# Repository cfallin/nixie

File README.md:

These are the raw Eagle schematic/PCB design files and the AVR firmware for a
Nixie tube clock.

Nixie tubes are gas-discharge neon display tubes. They take ~150 volts at a few
milliamps and glow a soft, pleasing orange. Each digit is a separate cathode in
a particular shape, so the numerals look more natural than more contemprary
7-segment display designs.

This project is a small microcontroller-based digital clock using 6 nixie tubes
(for HH:MM:SS). An ATmega16 8-bit AVR microcontroller keeps time based on its
20MHz system clock provided by a crystal oscillator, and controls six digit
driver ICs, one per Nixie tube. Each driver has high-voltage open-collector
outputs capable of directly interfacing with the display tube cathodes. The 150
volt anode supply is provided by a small switched-inductor boost converter,
which uses a power MOSFET driven by the microcontroller's PWM generator. The
design includes a feedback loop to an analog-to-digital (ADC) input on the AVR
so that it can regulate the tube voltage precisely.

Nixies can be found in various places online and often come from Russia. I
found mine on Etsy. Prices vary but I think the retro glow is well worth the
cost :-) The 74141 Nixie driver chips are also somewhat rare (e.g., not stocked
by Digikey) but can be found on eBay or at other small shops online.

=== DEVELOPMENT ENVIRONMENT ===

The firmware is written in C to be cross-compiled by avr-gcc. It assumes the
standard AVR headers that come with that compiler. The Makefile includes a
target to program the flash and fuses on the AVR using avrdude, but other
programmers can also be used.

The schematic and board were drawn in Eagle CAD. The additional libraries used
are included here.

=== IN PROGRESS ===

Work is currently in progress; in particular, the firmware is specific to an
earlier (hand-built) prototype version of the hardware and DOES NOT MATCH the
board. The board is currently (Feb 2014) out for a prototype run; when I build
the hardware designed here I'll update the firmware as appropriate.

=== LICENSE ===

All code, schematics and board design files here are Copyright (c) 2014 Chris
Fallin <cfallin@c1f.net>. Provided under the GNU GPL v2.

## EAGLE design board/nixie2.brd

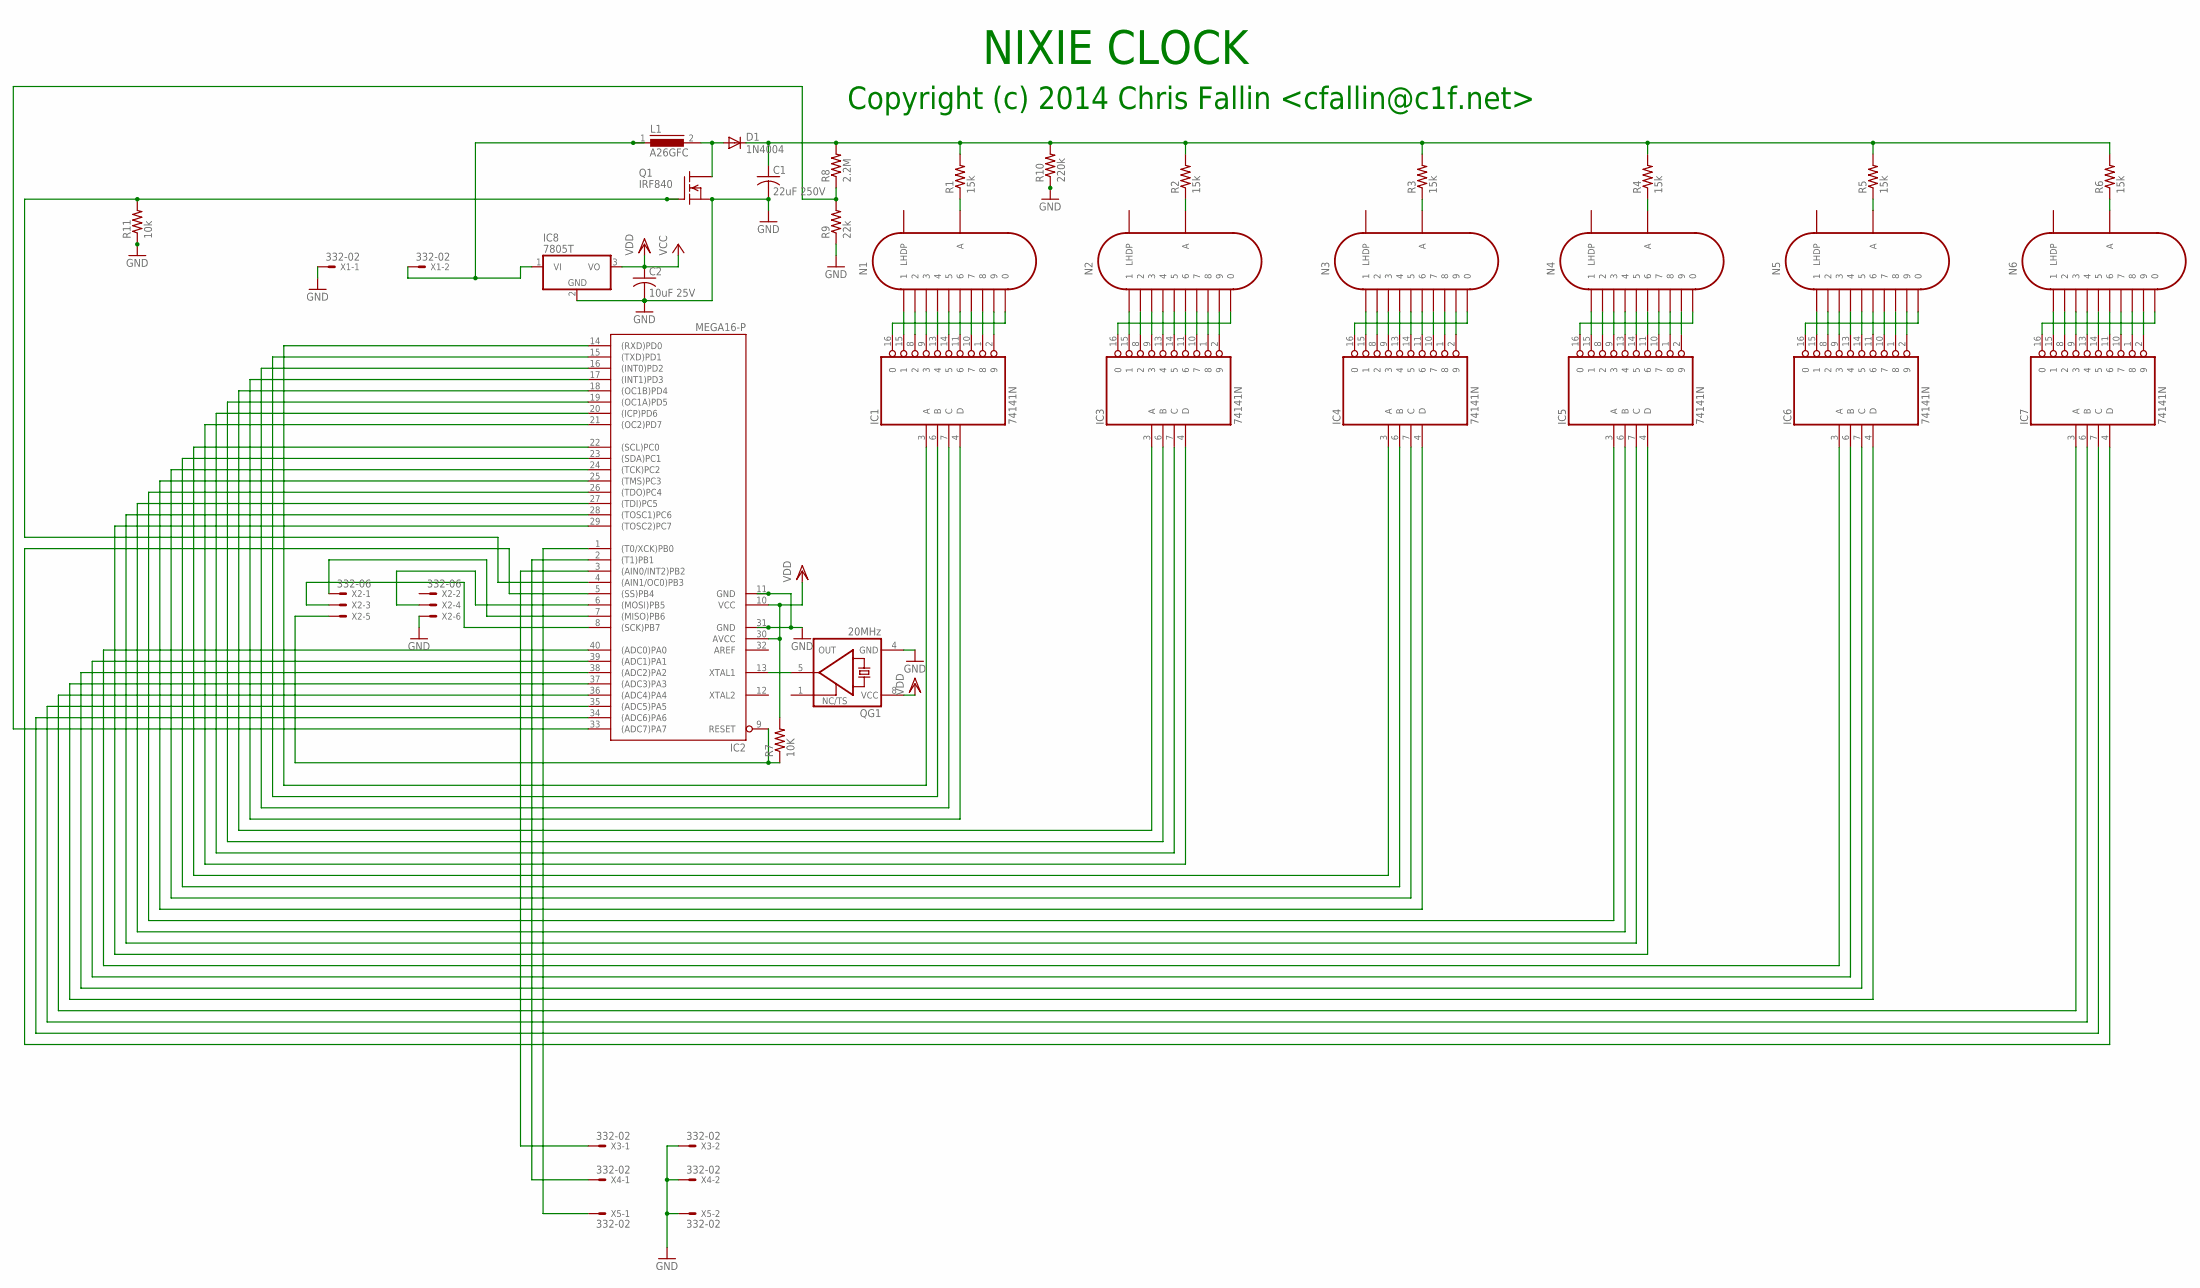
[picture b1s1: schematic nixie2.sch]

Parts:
C1: 22uF 250V; C050-075X075
C2: 10uF 25V; C050-075X075
D1: 1N4004; DO41-10
IC1, IC3, IC4, IC5, IC6, IC7: 74141N; DIL16
IC2: MEGA16-P; DIL40
IC8: 7805T; TO220H
L1: A26GFC
N1, N2, N3, N4, N5, N6: IN-12B; IN-12
Q1: IRF840; TO220
QG1: 20MHz; DIL08S
R1, R2, R3, R4, R5, R6: 15k; 0204V
R7: 10K; 0204V
R8: 2.2M; 0204V
R9: 22k; 0204V
R10: 220k; 0204V
R11: 10k; 0204V
X1, X3, X4, X5: 332-02
X2: 332-06

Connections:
GND: C1.2, C2.2, IC1.12 (GND), IC2.11 (GND), IC2.31 (GND), IC3.12 (GND), IC4.12 (GND), IC5.12 (GND), IC6.12 (GND), IC7.12 (GND), IC8.2 (GND), Q1.3 (S), QG1.4 (GND), R9.1, R10.1, R11.1, X1.1, X2.6, X3.2, X4.2, X5.2
unnamed: IC1.15 (1), N1.1
unnamed: IC1.8 (2), N1.2
unnamed: IC1.9 (3), N1.3
unnamed: IC1.13 (4), N1.4
unnamed: IC1.14 (5), N1.5
unnamed: IC1.11 (6), N1.6
unnamed: IC1.10 (7), N1.7
unnamed: IC1.1 (8), N1.8
unnamed: IC1.2 (9), N1.9
unnamed: N1.A, R1.1
unnamed: IC3.15 (1), N2.1
unnamed: IC3.8 (2), N2.2
unnamed: IC3.9 (3), N2.3
unnamed: IC3.13 (4), N2.4
unnamed: IC3.14 (5), N2.5
unnamed: IC3.11 (6), N2.6
unnamed: IC3.10 (7), N2.7
unnamed: IC3.1 (8), N2.8
unnamed: IC3.2 (9), N2.9
unnamed: IC3.16 (0), N2.0
unnamed: N2.A, R2.1
unnamed: IC4.15 (1), N3.1
unnamed: IC4.8 (2), N3.2
unnamed: IC4.9 (3), N3.3
unnamed: IC4.13 (4), N3.4
unnamed: IC4.14 (5), N3.5
unnamed: IC4.11 (6), N3.6
unnamed: IC4.10 (7), N3.7
unnamed: IC4.1 (8), N3.8
unnamed: IC4.2 (9), N3.9
unnamed: IC4.16 (0), N3.0
unnamed: N3.A, R3.1
unnamed: IC5.15 (1), N4.1
unnamed: IC5.8 (2), N4.2
unnamed: IC5.9 (3), N4.3
unnamed: IC5.13 (4), N4.4
unnamed: IC5.14 (5), N4.5
unnamed: IC5.11 (6), N4.6
unnamed: IC5.10 (7), N4.7
unnamed: IC5.1 (8), N4.8
unnamed: IC5.2 (9), N4.9
unnamed: IC5.16 (0), N4.0
unnamed: N4.A, R4.1
unnamed: IC6.15 (1), N5.1
unnamed: IC6.8 (2), N5.2
unnamed: IC6.9 (3), N5.3
unnamed: IC6.13 (4), N5.4
unnamed: IC6.14 (5), N5.5
unnamed: IC6.11 (6), N5.6
unnamed: IC6.10 (7), N5.7
unnamed: IC6.1 (8), N5.8
unnamed: IC6.2 (9), N5.9
unnamed: IC6.16 (0), N5.0
unnamed: N5.A, R5.1
unnamed: IC7.15 (1), N6.1
unnamed: IC7.8 (2), N6.2
unnamed: IC7.9 (3), N6.3
unnamed: IC7.13 (4), N6.4
unnamed: IC7.14 (5), N6.5
unnamed: IC7.11 (6), N6.6
unnamed: IC7.10 (7), N6.7
unnamed: IC7.1 (8), N6.8
unnamed: IC7.2 (9), N6.9
unnamed: IC7.16 (0), N6.0
unnamed: N6.A, R6.1
unnamed: C1.1, D1.C, R1.2, R2.2, R3.2, R4.2, R5.2, R6.2, R8.2, R10.2
unnamed: IC2.13 (XTAL1), QG1.5 (OUT)
unnamed: IC2.6 ((MOSI)PB5), X2.4
unnamed: D1.A, L1.2, Q1.2 (D)
unnamed: IC8.1 (VI), L1.1, X1.2
unnamed: IC2.7 ((MISO)PB6), X2.1
unnamed: IC2.8 ((SCK)PB7), X2.3
unnamed: IC2.9 (RESET), R7.1, X2.5
unnamed: IC1.3 (A), IC2.14 ((RXD)PD0)
unnamed: IC1.6 (B), IC2.15 ((TXD)PD1)
unnamed: IC1.7 (C), IC2.16 ((INT0)PD2)
unnamed: IC1.4 (D), IC2.17 ((INT1)PD3)
unnamed: IC2.18 ((OC1B)PD4), IC3.3 (A)
unnamed: IC2.19 ((OC1A)PD5), IC3.6 (B)
unnamed: IC2.20 ((ICP)PD6), IC3.7 (C)
unnamed: IC2.21 ((OC2)PD7), IC3.4 (D)
unnamed: IC2.22 ((SCL)PC0), IC4.3 (A)
unnamed: IC2.23 ((SDA)PC1), IC4.6 (B)
unnamed: IC2.24 ((TCK)PC2), IC4.7 (C)
unnamed: IC2.25 ((TMS)PC3), IC4.4 (D)
unnamed: IC2.26 ((TDO)PC4), IC5.3 (A)
unnamed: IC2.27 ((TDI)PC5), IC5.6 (B)
unnamed: IC2.28 ((TOSC1)PC6), IC5.7 (C)
unnamed: IC2.29 ((TOSC2)PC7), IC5.4 (D)
unnamed: IC2.4 ((AIN1/OC0)PB3), Q1.1 (G), R11.2
unnamed: IC2.40 ((ADC0)PA0), IC6.3 (A)
unnamed: IC2.39 ((ADC1)PA1), IC6.6 (B)
unnamed: IC2.38 ((ADC2)PA2), IC6.7 (C)
unnamed: IC2.37 ((ADC3)PA3), IC6.4 (D)
unnamed: IC2.36 ((ADC4)PA4), IC7.3 (A)
unnamed: IC2.35 ((ADC5)PA5), IC7.6 (B)
unnamed: IC2.34 ((ADC6)PA6), IC7.7 (C)
unnamed: IC2.5 ((SS)PB4), IC7.4 (D)
unnamed: IC2.33 ((ADC7)PA7), R8.1, R9.2
unnamed: IC2.3 ((AIN0/INT2)PB2), X3.1
unnamed: IC2.2 ((T1)PB1), X4.1
unnamed: IC2.1 ((T0/XCK)PB0), X5.1
unnamed: IC1.16 (0), N1.0
VDD: C2.1, IC1.5 (VCC), IC2.10 (VCC), IC2.30 (AVCC), IC3.5 (VCC), IC4.5 (VCC), IC5.5 (VCC), IC6.5 (VCC), IC7.5 (VCC), IC8.3 (VO), QG1.8 (VCC), R7.2

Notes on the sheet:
NIXIE CLOCK
Copyright (c) 2014 Chris Fallin <cfallin@c1f.net>

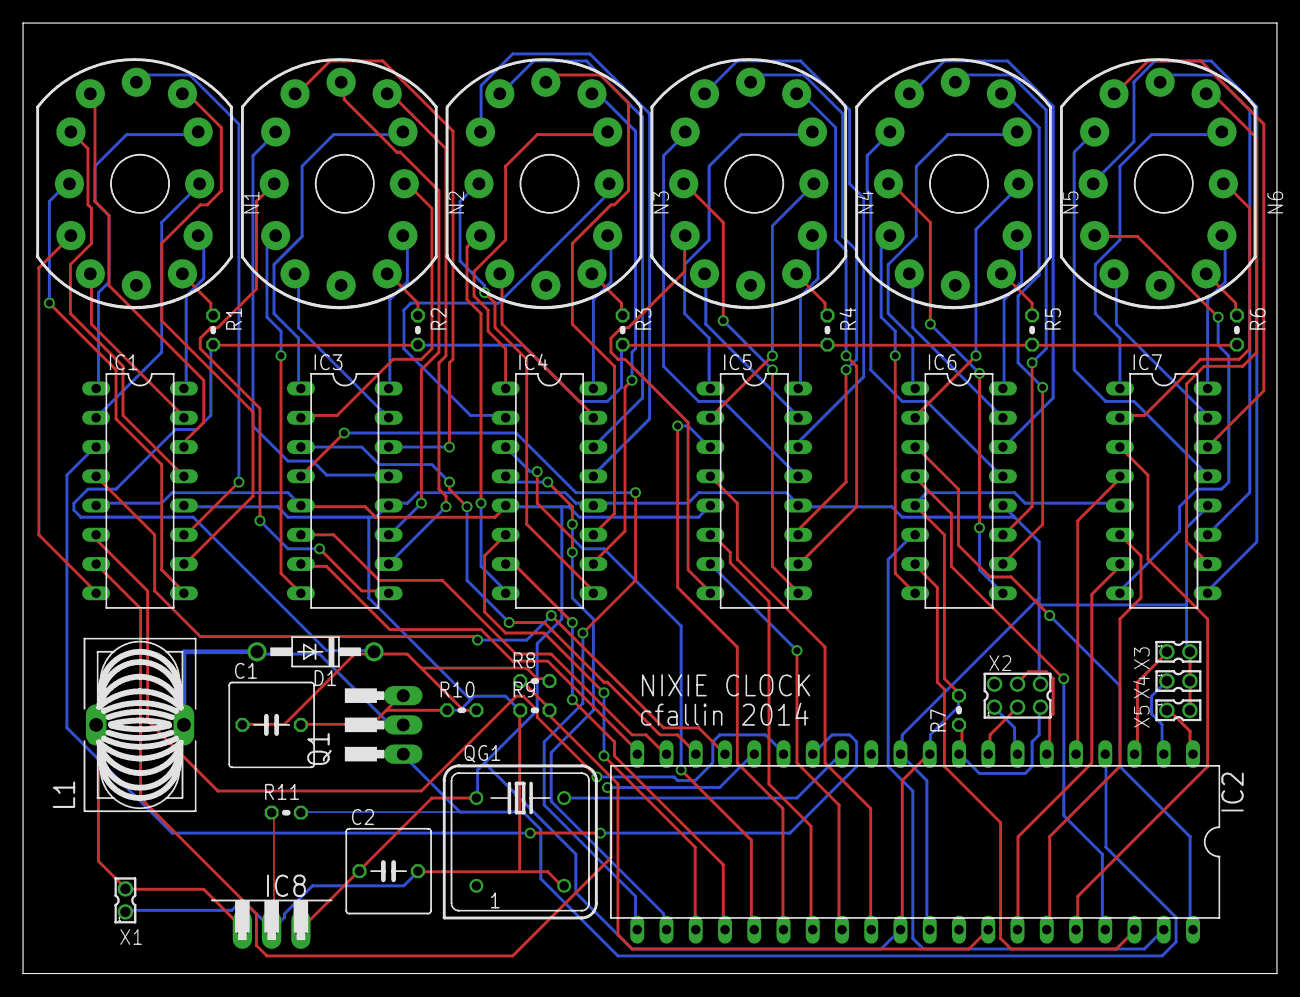
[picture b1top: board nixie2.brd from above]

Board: 2 copper layers, 108.9 x 82.5 mm, 36 parts (0 on the bottom side), 105 nets.

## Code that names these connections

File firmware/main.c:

/*
 * Nixie Clock
 *
 * Copyright (c) 2014 Chris Fallin <cfallin@c1f.net>
 * Placed under the GNU GPL v2.
 */

/* 
 * Assume an ATmega16.
 *
 * IO connections (manufactured board version):
 *
 * PD0..PD3 are BCD for H-tens digit.
 * PD4..PD7 are BCD for H-ones digit.
 * PC0..PC3 are BCD for M-tens digit.
 * PC4..PC7 are BCD for M-ones digit.
 * PA0..PA3 are BCD for S-tens digit.
 * PA4,PA5,PA6,PB4 are BCD for S-ones digit.
 *
 * PB3/OC0 is gate for power MOSFET on high-voltage boost converter.
 *
 * PA7 is analog feedback on high-voltage bus (1/101 resistive prescaler).
 *
 * PB0, PB1, PB2 are pushbuttons 1, 2, 3.
 */

#include <avr/io.h>
#include <avr/interrupt.h>

/* local functions */
static void init_time();
static void one_second();

static void init_display();
static void write_digit(char digit);
static void write_display();
static void init_buttons();
static void check_buttons();
static void init_smps();
static void adjust_smps();

typedef struct {
    unsigned char H, M, S;
    unsigned char ticks, correction;
} hms_time_t;

hms_time_t current_time;

unsigned char debounce_H, debounce_M, debounce_S;
unsigned char registered_H, registered_M, registered_S;

void init_time()
{
    current_time.H = current_time.M = current_time.S = 0;
    current_time.ticks = current_time.correction = 0;
    
    // set up timer 2
    TCNT2 = 0;
    TCCR2 = 0x47; // WGM mode 2 -- CTC (reset on match); clock source prescaler/1024
    OCR2 = 249;   // for a 20MHz clock, 20 / 1024 / 250 -> 78.125 Hz timer interrupt
    TIFR |= 0x80; // clear interrupt flag
    TIMSK |= 0x80; // enable timer 2 interrupt
    ASSR = 0; // disable asynchronous operation (external counts)
}

ISR(TIMER2_COMP_vect)
{
    adjust_smps();

    // increment 'ticks'; after 78.125 ticks, one second has elapsed.
    // We manage the fractional part by bumping the second display at
    // 78 ticks, but keeping a fractional part that's incremented
    // on each second. When the fractional part reaches 7, we wait an
    // extra tick to bump the second count.
    current_time.ticks++;

    if (current_time.ticks == 78) {

        one_second();

        current_time.ticks = 0;
        current_time.correction++;
        if (current_time.correction == 8) {
            current_time.correction = 0;
            current_time.ticks = 0xFF; // take an extra tick next second
        }
    }

    check_buttons();
}

void one_second()
{
    current_time.S++;
    if (current_time.S == 60) {
        current_time.S = 0;
        current_time.M++;
    }
    if (current_time.M == 60) {
        current_time.M = 0;
        current_time.H++;
    }
    if (current_time.H == 24) {
        current_time.H = 0;
    }

    write_display();
}

void init_display()
{
    // PD0..7, PC0..7, PA0..6, PB4 are outputs.
    // Start out with 0b1111 on all digits (digit blanked).
    PORTD = 0xff;
    DDRD = 0xff;
    PORTC = 0xff;
    DDRC = 0xff;
    PORTA |= 0x7f;
    DDRA |= 0x7f;
    PORTB |= 0x10;
    DDRB |= 0x10;
}

char lookup_ones[] = {
    0, 1, 2, 3, 4, 5, 6, 7, 8, 9,
    0, 1, 2, 3, 4, 5, 6, 7, 8, 9,
    0, 1, 2, 3, 4, 5, 6, 7, 8, 9,
    0, 1, 2, 3, 4, 5, 6, 7, 8, 9,
    0, 1, 2, 3, 4, 5, 6, 7, 8, 9,
    0, 1, 2, 3, 4, 5, 6, 7, 8, 9, };
char lookup_tens[] = {
    0, 0, 0, 0, 0, 0, 0, 0, 0, 0,
    1, 1, 1, 1, 1, 1, 1, 1, 1, 1,
    2, 2, 2, 2, 2, 2, 2, 2, 2, 2,
    3, 3, 3, 3, 3, 3, 3, 3, 3, 3,
    4, 4, 4, 4, 4, 4, 4, 4, 4, 4,
    5, 5, 5, 5, 5, 5, 5, 5, 5, 5, };

void write_display()
{
    // Hours and minutes are straight BCD out to the decoder/driver chips.
    // Note that ones digit of each is on high nibble rather than low nibble.
    PORTD = (lookup_tens[current_time.H]) | (lookup_ones[current_time.H] << 4);
    PORTC = (lookup_tens[current_time.M]) | (lookup_ones[current_time.M] << 4);

    // Seconds output has MSB on PB4 rather than PA7.
    uint8_t s = (lookup_tens[current_time.M]) | (lookup_ones[current_time.M] << 4);
    PORTA = (PORTA & 0x80) | (s & 0x7f);
    PORTB = (PORTB & 0xef) | ((s & 0x80) >> 3);
}

void init_buttons()
{
    DDRD &= ~0x07; // PD0, PD1, PD2 are inputs (H, M, S)

    debounce_H = debounce_M = debounce_S = 0;
    registered_H = registered_M = registered_S = 0;
}

void check_buttons()
{
    return;

    // check once per 78.125Hz tick. Three ticks with a '1' is sufficiently debounced
    // to register a button-press.
    
    if ((PINB & 0x01) && debounce_H < 3) // H button
        debounce_H++;
    else {
        debounce_H = 0;
        registered_H = 0;
    }
    if ((PINB & 0x02) && debounce_M < 3) // M button
        debounce_M++;
    else {
        debounce_M = 0;
        registered_M = 0;
    }
    if ((PINB & 0x04) && debounce_S < 3) // S-clear button
        debounce_S++;
    else {
        debounce_S = 0;
        registered_S = 0;
    }

    if (debounce_H == 3 && !registered_H) {
        current_time.H++;
        if (current_time.H == 24) current_time.H = 0;
        registered_H = 1;
    }
    if (debounce_M == 3 && !registered_M) {
        current_time.M++;
        if (current_time.M == 60) current_time.M = 0;
        registered_M = 1;
    }
    if (debounce_S == 3 && !registered_S) {
        current_time.S = 0;
        registered_S = 1;
    }
}

static void init_smps()
{
    //TCCR0 = (1<<WGM00) | (1<<WGM01) | (1<<COM01) | (1<<CS00);
    //OCR0 = 0x40;

    // set up OC0 (PB3) output, low by default until timer is set up
    PORTB &= ~8;
    DDRB |= 8;

    DDRA = 0xff;
    PORTA = 0;

    while (1) {
        PORTB |= 0x08;
        PORTB &= ~0x08;
        PORTA |= 1;
        PORTA &= ~1;
        asm volatile("nop; nop");
    }

    // set up ADC on voltage feedback pin
    ADMUX = 0xe0;  // 2.56V internal Vref, ADC0 (PC0) input, left-adjust result
    ADCSRA = 0xe7; // enable, start conversion, free-running, interrupts disabled, prescaler at clk/128

}

char __level = 0;

void adjust_smps()
{
    return;

    char val = ADCH;
    char target = 170; // 170 volts (voltage divider is 100:1; units of ADCH with 2.56V ref are 0.01V

    if (val > 190) { // safety shutoff at 190V
        OCR1A = 0;
    }
    if (val < target) {
        if (OCR1A < 0xa0) OCR1A++;
    }
    if (val > target) {
        if (OCR1A > 0) OCR1A--;
    }
}

int main()
{
    DDRB = 1;
    PORTB = 0;
    while(1) { PORTB ^= 1; }
    //init_time(); // initialize the time
    //init_display();
    //init_buttons();
    init_smps();
#if 1
    sei(); // enable interrupts
    while (1);

#else
    one_second();
    one_second();
    one_second();
    current_time.S = 9;

    while(1) write_display();
#endif
}

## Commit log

2014-01-25 Initial commit.
2014-01-26 Some work on initial (untested) firmware
2014-01-26 Debugging work
2014-01-27 test code
2014-02-06 Image export of board.
2014-02-06 Schematic printout
2014-02-06 Included additional libraries and PCB shop design rules.
2014-02-07 Moved all Eagle design files to board/.
2014-02-07 Moved firmware to firmware/.
2014-02-07 Added README; updated license and comments in firmware.
2014-02-24 Firmware update for ATmega16 and PCB pinout.
